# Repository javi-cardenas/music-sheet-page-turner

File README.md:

# Sheet Music Page Turner

This page-turning device was designed with reading and multitasking in mind. While devices for eBooks already exist, our solution primarily aimed to provide a cheaper hands-free alternative for physical sheet music books.

<div align="center">
  <h2>Minimum Viable Product</h2>
</div>

Our page turner uses two foot pedals as input and three servo motors to turn pages forward or backward. The servo motors are attached to the base of a wooden stand and a liquid crystal display (LCD) is mounted to a metal enclosure.

Ultimately, the device was successfully able to turn pages in both directions, consecutively turn up to 10 pages in a row, and digitally track the number of pages the user turned.

**Note:** Feel free to take any inspiration, but this code was not intended to be cloned and deployed. As such, I do not provide support or guidance for this.

<div align="center">
  <h2>Software Flow Chart</h2>
  
</div>

<div align="center">
  <h2>Block Diagram</h2>
  
</div>

<div align="center">
  <h2>Circuit Schematic</h2>
  
</div>

<div align="center">
  <h2>Printable Circuit Board (PCB) Diagram</h2>
  
</div>

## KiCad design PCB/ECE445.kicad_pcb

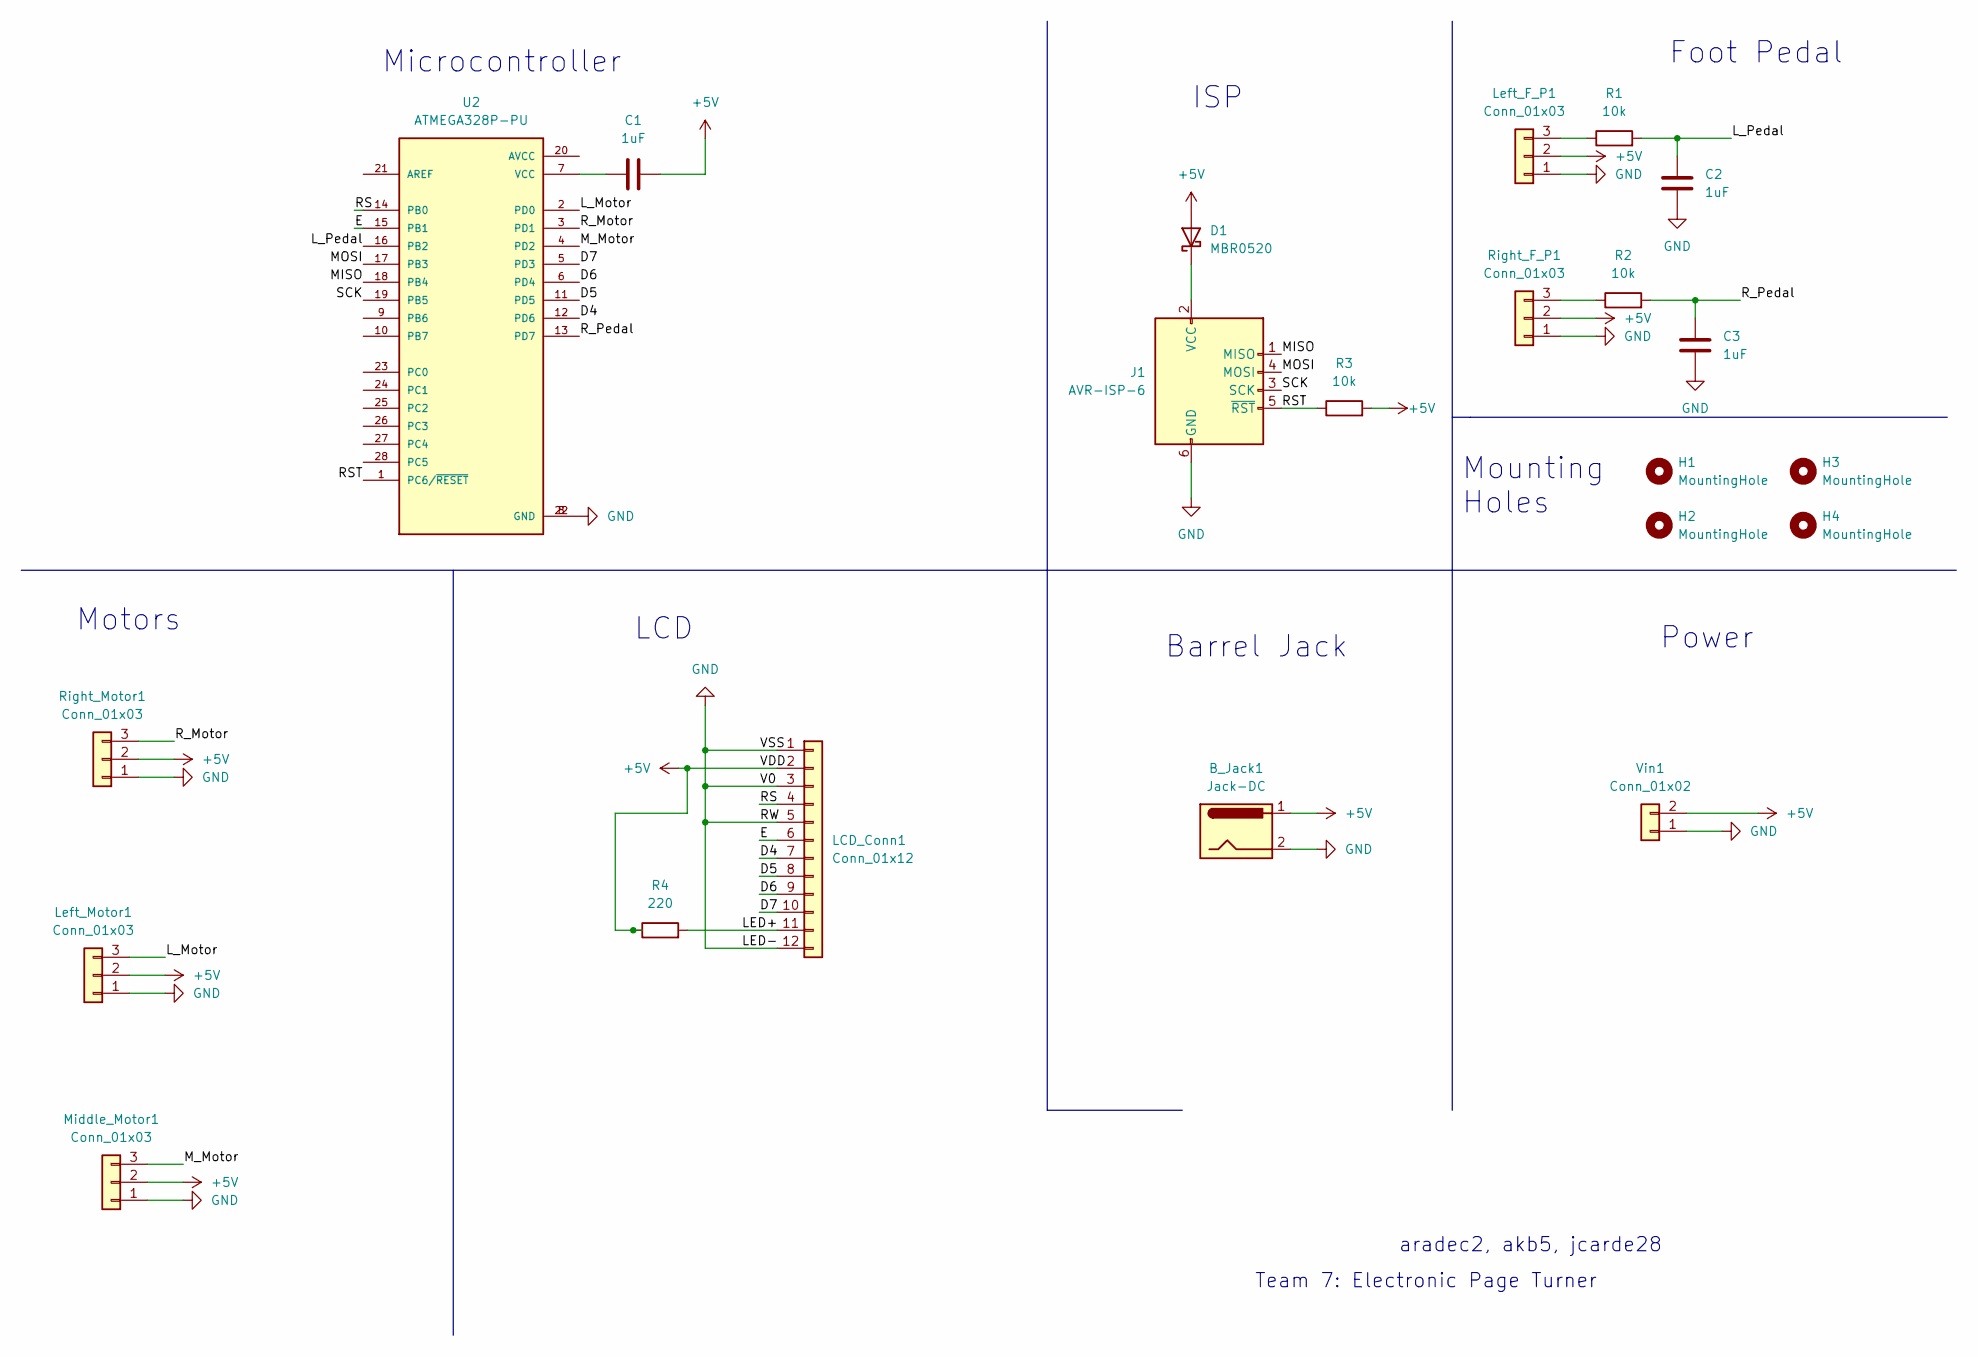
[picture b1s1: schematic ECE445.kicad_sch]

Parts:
B_Jack1: Jack-DC; BarrelJack_Horizontal
C1, C2, C3: 1uF; C_0805_2012Metric_Pad1.18x1.45mm_HandSolder
D1: MBR0520; D_SOD-123
H1, H2, H3, H4: MountingHole; MountingHole_3.2mm_M3
J1: AVR-ISP-6; IDC-Header_2x03_P2.54mm_Vertical
LCD_Conn1: Conn_01x12; Molex_KK-254_AE-6410-12A_1x12_P2.54mm_Vertical
Left_F_P1: Conn_01x03; Molex_KK-254_AE-6410-03A_1x03_P2.54mm_Vertical
Left_Motor1: Conn_01x03; Molex_KK-254_AE-6410-03A_1x03_P2.54mm_Vertical
Middle_Motor1: Conn_01x03; Molex_KK-254_AE-6410-03A_1x03_P2.54mm_Vertical
R1, R2, R3: 10k; R_0805_2012Metric_Pad1.20x1.40mm_HandSolder
R4: 220; R_0805_2012Metric_Pad1.20x1.40mm_HandSolder
Right_F_P1: Conn_01x03; Molex_KK-254_AE-6410-03A_1x03_P2.54mm_Vertical
Right_Motor1: Conn_01x03; Molex_KK-254_AE-6410-03A_1x03_P2.54mm_Vertical
U2: ATMEGA328P-PU; DIP794W46P254L2967H457Q28B
Vin1: Conn_01x02; Molex_KK-254_AE-6410-02A_1x02_P2.54mm_Vertical

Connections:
+5V: B_Jack1.1, C1.2, D1.2 (A), LCD_Conn1.2, Left_F_P1.2, Left_Motor1.2, Middle_Motor1.2, R3.2, R4.1, Right_F_P1.2, Right_Motor1.2, Vin1.2; also elsewhere on the board
/D4: LCD_Conn1.7, U2.12 (PD6)
/D5: LCD_Conn1.8, U2.11 (PD5)
/D6: LCD_Conn1.9, U2.6 (PD4)
/D7: LCD_Conn1.10, U2.5 (PD3)
/E: LCD_Conn1.6, U2.15 (PB1)
/LED+: LCD_Conn1.11, R4.2; also elsewhere on the board
/L_Motor: Left_Motor1.3, U2.2 (PD0)
/L_Pedal: C2.1, R1.2, U2.16 (PB2)
/MISO: J1.1 (MISO), U2.18 (PB4)
/MOSI: J1.4 (MOSI), U2.17 (PB3)
/M_Motor: Middle_Motor1.3, U2.4 (PD2)
/RS: LCD_Conn1.4, U2.14 (PB0)
/RST: J1.5 (~RST), R3.1, U2.1 (PC6/~RESET)
/R_Motor: Right_Motor1.3, U2.3 (PD1)
/R_Pedal: C3.1, R2.2, U2.13 (PD7)
/SCK: J1.3 (SCK), U2.19 (PB5)
GND: B_Jack1.2, C2.2, C3.2, J1.6 (GND), LCD_Conn1.1, LCD_Conn1.3, LCD_Conn1.5, LCD_Conn1.12, Left_F_P1.1, Left_Motor1.1, Middle_Motor1.1, Right_F_P1.1, Right_Motor1.1, U2.8 (GND), U2.22 (GND), Vin1.1
unnamed: C1.1, U2.7 (VCC)
unnamed: D1.1 (K), J1.2 (VCC)
unnamed: Left_F_P1.3, R1.1
unnamed: R2.1, Right_F_P1.3

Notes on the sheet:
ISP
Team 7: Electronic Page Turner
Mounting Holes
Microcontroller
aradec2, akb5, jcarde28
Power
Foot Pedal
LCD
Motors
Barrel Jack

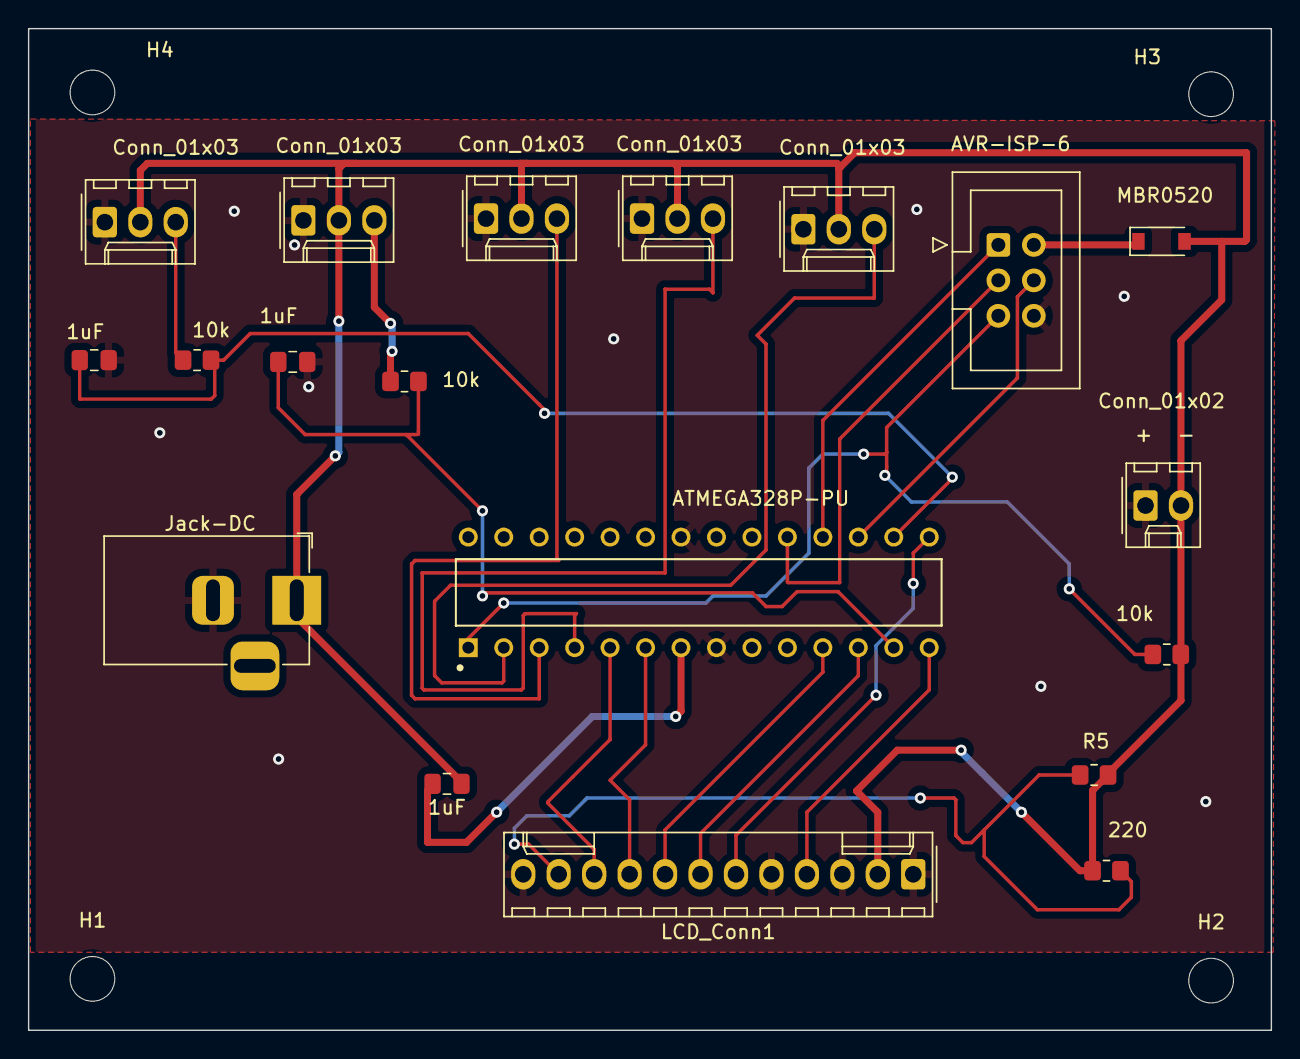
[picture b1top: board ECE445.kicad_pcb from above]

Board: 2 copper layers, 89.0 x 71.8 mm, 23 parts (0 on the bottom side), 22 nets.

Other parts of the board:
R5: R5; R_0805_2012Metric_Pad1.20x1.40mm_HandSolder

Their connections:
+5V: R5.2; also elsewhere on the board
/LED+: R5.1; also elsewhere on the board

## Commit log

2025-02-06 added .gitignore
2025-02-06 updated docs
2025-02-06 cropped imgs
2025-02-06 Create LICENSE
2025-02-06 remove imgs
